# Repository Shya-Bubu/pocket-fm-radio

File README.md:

# FM Pocket Radio

This repository contains the complete design and documentation for an FM Pocket Radio project, developed as part of the **EE2050 Design Principles and Manufacturing Technologies** module at the University of Peradeniya (Semester 3).

The project demonstrates an iterative engineering approach, evolving from an initial proof-of-concept perfboard build to an ESP32-powered dot-board prototype with an OLED UI, and finally into a custom mixed-signal 2-layer PCB design.

## Project Structure
- **[FM_Pocket_Radio_Report.pdf](FM_Pocket_Radio_Report.pdf)**: Complete engineering report covering system architecture, circuit schematics, hardware iterations, and debugging logs.
- **[radio 2.kicad_pcb](radio%202.kicad_pcb)**: KiCad 9.0 PCB layout for the final Phase 3 custom 2-layer board (70 x 50 mm).
- **images/**: High-resolution prototype photos, KiCad schematics, and 2D/3D board renders.

## Highlights
- **Iterative Hardware Evolution**:
  - **Iteration 1 (Proof of Concept)**: Arduino UNO + RDA5807M FM receiver + TDA2822M audio amplifier on perfboard.
  - **Iteration 2 (Dot Board Prototype)**: ESP32 DevKit + RDA5807M + TDA2822M (BTL mode) + SH1106 1.3" OLED display + dual rotary encoders + 18650 Li-ion battery. Features a 68-station Sri Lankan FM station database and dynamic UI.
  - **Iteration 3 (Custom PCB)**: Standalone ATmega328P microcontroller + RDA5807M + PAM8403 Class-D stereo amplifier + CH340C USB-UART bridge + TP4056/DW01A battery management + single USB-C port for power, charging, and flashing.
- **Documentation**: See [FM_Pocket_Radio_Report.pdf](FM_Pocket_Radio_Report.pdf) for a deep dive into the technical architecture, challenges, and iterative prototyping process.

## Prototypes & PCB Design

### Iteration 2: Working Hardware Prototype

Fully working dot-board prototype with OLED station readout, rotary volume and tuning control, and integrated battery management.

### Iteration 3: KiCad PCB Design (2D Layout & 3D Render)

Custom 2-layer 70 x 50 mm PCB with dedicated analog, digital, and power zone isolation.

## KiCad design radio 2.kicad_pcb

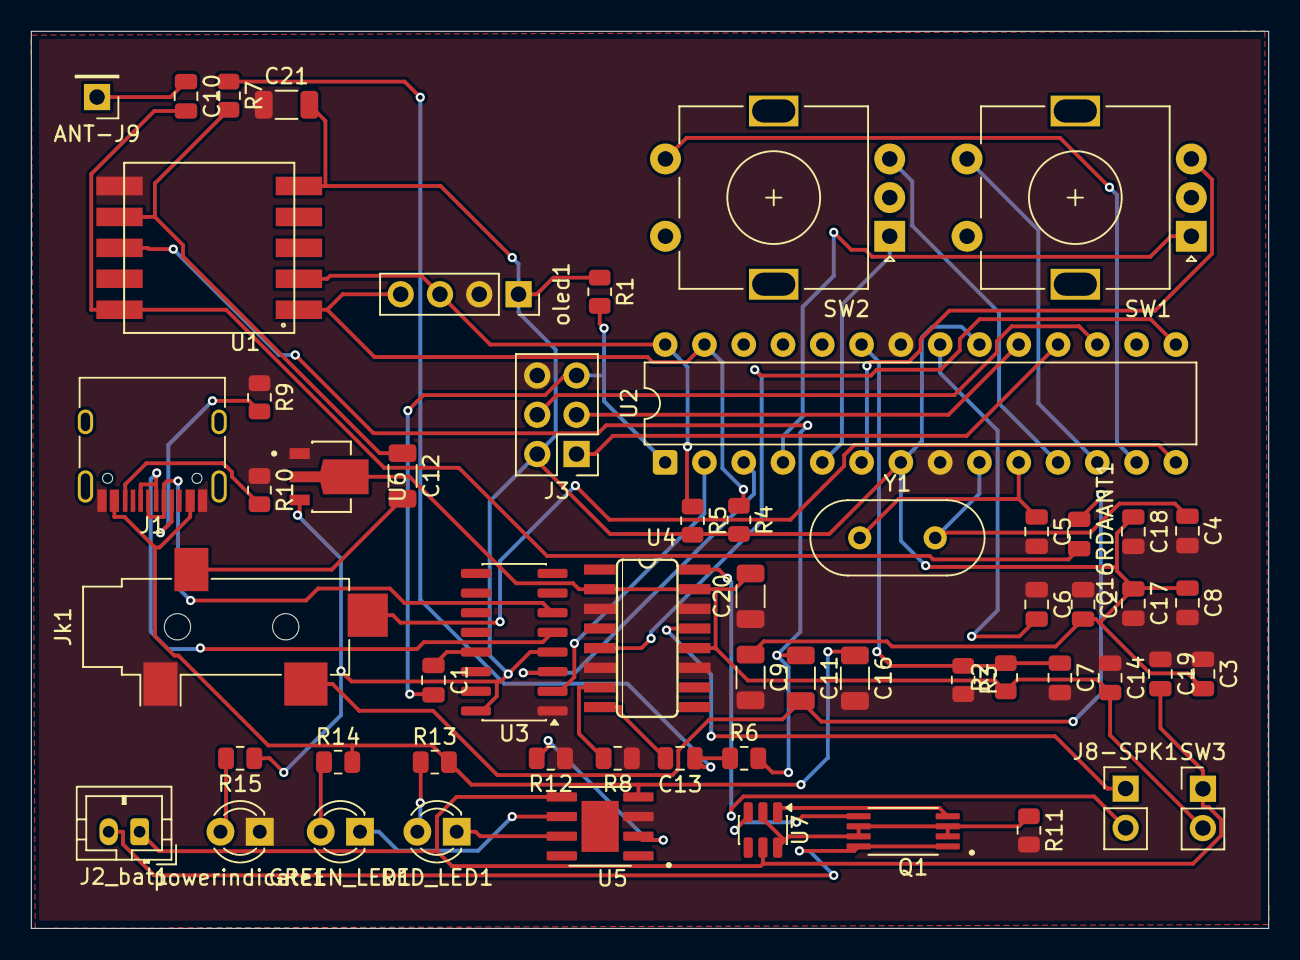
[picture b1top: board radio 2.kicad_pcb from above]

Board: 2 copper layers, 80.0 x 58.0 mm, 58 parts (0 on the bottom side), 51 nets.

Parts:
ANT-J9: Conn_01x01; PinHeader_1x01_P2.54mm_Vertical
C1, C2, C3, C6, C7, C8, C14, C17, C18: 100nF; C_0805_2012Metric
C4, C5: 22pF; C_0805_2012Metric
C9, C11, C12, C16, C20, C21: 10uF; C_1206_3216Metric
C10, C16RDAANT1: 100pF; C_0805_2012Metric
C13, C19: 1uF; C_0805_2012Metric
GREEN_LED1: LED; LED_D3.0mm
J1: USB_C_Receptacle_USB2.0_16P; USB_C_Receptacle_HRO_TYPE-C-31-M-12
J2_bat1: Conn_01x02; JST_PH_B2B-PH-K_1x02_P2.00mm_Vertical
J3: Conn_02x03_Counter_Clockwise; PinHeader_2x03_P2.54mm_Vertical
J8-SPK1: Conn_01x02; PinHeader_1x02_P2.54mm_Vertical
Jk1: AudioJack3_SwitchT; Jack_3.5mm_CUI_SJ-3524-SMT_Horizontal
Q1: FS8205A; SOP65P640X120-8N
R1, R6, R7, R8: 10k; R_0805_2012Metric
R2, R3: 100k; R_0805_2012Metric
R4, R5: 4.7k; R_0805_2012Metric
R9, R10: 5.1k; R_0805_2012Metric
R11: 100; R_0805_2012Metric
R12: 2.2k; R_0805_2012Metric
R13, R14: 1k; R_0805_2012Metric
R15: 330; R_0805_2012Metric
RED_LED1: LED; LED_D3.0mm
SW1, SW2: RotaryEncoder_Switch; RotaryEncoder_Alps_EC11E-Switch_Vertical_H20mm
SW3: SW_SPST; PinHeader_1x02_P2.54mm_Vertical
U1: RDA5807M
U2: ATMEGA328P-PU; DIP-28_W7.62mm
U3: CH340C; SOIC-16_3.9x9.9mm_P1.27mm
U4: PAM8403; SOP-16
U5: TP4056; SOP127P600X175-9N
U6: HT7333; IC_HT7333
U7: DW01A; SOT-23-6
Y1: Crystal; Crystal_HC49-4H_Vertical
oled1: Conn_01x04; PinSocket_1x04_P2.54mm_Vertical
powerindicate1: LED; LED_D3.0mm

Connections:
+3V3: C2.2, C3.2, C8.1, C9.1, C17.1, C18.1, C21.2, J3.2, R1.1, R4.2, R5.2, R15.1, U1.VCC, U2.7 (VCC), U2.20 (AVCC), U3.4 (V3), U3.16 (VCC), U6.3 (VOUT), oled1.1
/1: R4.1, U1.SDA, U2.27 (PC4), oled1.4
/2: R5.1, U1.SCL, U2.28 (PC5), oled1.3
/6: C10.2, C16RDAANT1.2, U1.ANT
/8: C11.1, R6.2, U1.L (LOUT)
/9: C12.1, R7.2, U1.R (ROUT)
/VBAT: C14.2, C20.2, R2.1, SW3.2 (B), U4.2 (PVCC), U4.12 (VCC), U4.15 (PVCC), U6.2 (VIN)
GND: C2.1, C3.1, C4.2, C5.2, C6.1, C7.2, C8.2, C9.2, C14.1, C16.2, C17.2, C18.2, C19.1, C20.1, C21.1, J1.A1 (GND), J1.A12 (GND), J1.B1 (GND), J1.B12 (GND), J3.6, Jk1.S, R3.2, R8.1, R9.1, R10.1, R11.2, R12.1, U1.GND, U2.8 (GND), U2.22 (GND), U3.1 (GND), U4.3 (PGND), U4.6 (PGND), U4.11 (GND), U4.14 (PGND), U5.3 (GND), U6.1 (GND), oled1.2, powerindicate1.1 (K)
unnamed: ANT-J9.1, C10.1
unnamed: C11.2, C16RDAANT1.1, Jk1.T
unnamed: C12.2, Jk1.R
unnamed: C13.1, R6.1, R7.1
unnamed: GREEN_LED1.2 (A), R14.1
unnamed: GREEN_LED1.1 (K), U5.6 (~STDBY)
unnamed: J1.A5 (CC1), R9.2
unnamed: J1.B5 (CC2), R10.2
unnamed: C19.2, J2_bat1.1, SW3.1 (A), U5.5 (BAT), U7.5 (VCC)
unnamed: J2_bat1.2, Q1.1, Q1.8
unnamed: J3.1, U2.18 (PB4)
unnamed: J3.3, U2.19 (PB5)
unnamed: J3.4, U2.17 (PB3)
unnamed: C1.2, J3.5, R1.2, U2.1 (PC6/~RESET)
unnamed: J8-SPK1.1, U4.13 (OUTL-)
unnamed: J8-SPK1.2, U4.16 (OUTL+)
unnamed: R13.1, RED_LED1.2 (A)
unnamed: RED_LED1.1 (K), U5.7 (~CHRG)
unnamed: C6.2, U2.21 (AREF)
unnamed: Jk1.TN, U2.14 (PB0)
unnamed: U2.15 (PB1), U4.5 (~SHDN)
unnamed: C4.1, U2.9 (PB6), Y1.2
unnamed: C5.1, U2.10 (PB7), Y1.1
unnamed: C7.1, R2.2, R3.1, U2.23 (PC0)
unnamed: U2.2 (PD0), U3.2 (TXD)
unnamed: U2.3 (PD1), U3.3 (RXD)
unnamed: SW1.A, U2.4 (PD2)
unnamed: SW2.A, U2.5 (PD3)
unnamed: SW1.B, U2.6 (PD4)
unnamed: SW2.B, U2.11 (PD5)
unnamed: SW1.S1, U2.12 (PD6)
unnamed: SW2.S1, U2.13 (PD7)
unnamed: J1.A6 (D+), J1.B6 (D+), U3.5 (UD+)
unnamed: J1.A7 (D-), J1.B7 (D-), U3.6 (UD-)
unnamed: C1.1, U3.13 (~DTR)
unnamed: C13.2, U4.8 (INL)
unnamed: R8.2, U4.7 (INR)
unnamed: R12.2, U5.2 (PROG)
unnamed: C16.1, J1.A4 (VBUS), J1.A9 (VBUS), J1.B4 (VBUS), J1.B9 (VBUS), R13.2, R14.2, U5.4 (VCC)
unnamed: Q1.2, Q1.3, Q1.6, Q1.7, R11.1, U7.2 (CS), U7.6 (GND)
unnamed: Q1.5, U7.3 (OC)
unnamed: Q1.4, U7.1 (OD)
unnamed: R15.2, powerindicate1.2 (A)
